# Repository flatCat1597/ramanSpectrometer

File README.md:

ramanPi
the DIY 3D Printable Raman Spectrometer

This repository will no longer contain ANY updates to the project.  The new repository at gitLab will have the latest files.  The github repo will NO LONGER be updated.  Please check the repository at https://gitlab.com/ramanPi before using any of the files here to build a ramanPi.

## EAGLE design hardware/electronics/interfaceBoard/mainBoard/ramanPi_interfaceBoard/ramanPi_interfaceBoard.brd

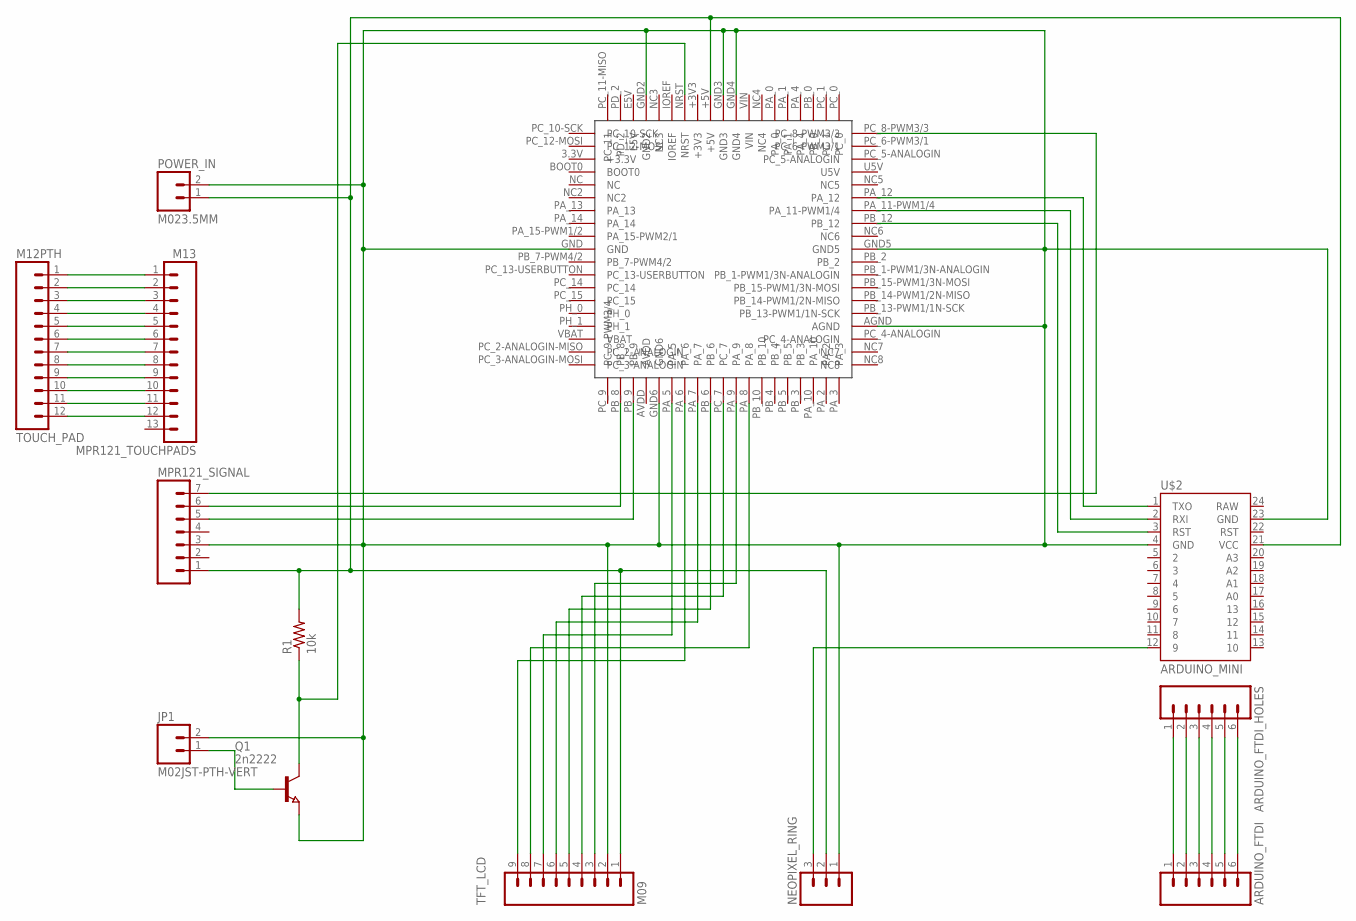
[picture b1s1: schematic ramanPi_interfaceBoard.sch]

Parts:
ARDUINO_FTDI: M06SIP; 1X06
ARDUINO_FTDI_HOLES: M06SIP; 1X06
JP1: M02JST-PTH-VERT; JST-2-PTH-VERT
MPR121_SIGNAL: M07; 1X07
MPR121_TOUCHPADS: M13; 1X13
NEOPIXEL_RING: M03JST-PTH-VERT; JST-3-PTH-VERT
POWER_IN: M023.5MM; SCREWTERMINAL-3.5MM-2
Q1: 2n2222; SOT23
R1: 10k; M1206
TFT_LCD: M09; 1X09
TOUCH_PAD: M12PTH; 1X12
U$1: STNUCLEOF401RE; F401-RE
U$2: ARDUINO_MINI

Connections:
+3.3V: U$1.3.3V (+3.3V)
+3V3: U$1.+3V3
+5V: MPR121_SIGNAL.1, NEOPIXEL_RING.2, POWER_IN.1, R1.2, TFT_LCD.1, U$1.+5V, U$2.21 (VCC)
AVDD: U$1.AVDD
E5V: U$1.E5V
GND: JP1.2, MPR121_SIGNAL.3, NEOPIXEL_RING.1, POWER_IN.2, Q1.2 (E), TFT_LCD.2, U$1.AGND, U$1.GND, U$1.GND2, U$1.GND3, U$1.GND4, U$1.GND5, U$1.GND6, U$2.4 (GND), U$2.23 (GND)
unnamed: MPR121_TOUCHPADS.1, TOUCH_PAD.1
unnamed: MPR121_TOUCHPADS.2, TOUCH_PAD.2
unnamed: MPR121_TOUCHPADS.3, TOUCH_PAD.3
unnamed: MPR121_TOUCHPADS.4, TOUCH_PAD.4
unnamed: MPR121_TOUCHPADS.5, TOUCH_PAD.5
unnamed: MPR121_TOUCHPADS.6, TOUCH_PAD.6
unnamed: MPR121_TOUCHPADS.7, TOUCH_PAD.7
unnamed: MPR121_TOUCHPADS.8, TOUCH_PAD.8
unnamed: MPR121_TOUCHPADS.9, TOUCH_PAD.9
unnamed: MPR121_TOUCHPADS.10, TOUCH_PAD.10
unnamed: MPR121_TOUCHPADS.11, TOUCH_PAD.11
unnamed: MPR121_TOUCHPADS.12, TOUCH_PAD.12
unnamed: NEOPIXEL_RING.3, U$2.12 (9)
unnamed: MPR121_SIGNAL.7, U$1.PC_8-PWM3/3
unnamed: MPR121_SIGNAL.5, U$1.PB_9
unnamed: MPR121_SIGNAL.6, U$1.PB_8
unnamed: ARDUINO_FTDI.1, ARDUINO_FTDI_HOLES.1
unnamed: ARDUINO_FTDI.2, ARDUINO_FTDI_HOLES.2
unnamed: ARDUINO_FTDI.3, ARDUINO_FTDI_HOLES.3
unnamed: ARDUINO_FTDI.4, ARDUINO_FTDI_HOLES.4
unnamed: ARDUINO_FTDI.5, ARDUINO_FTDI_HOLES.5
unnamed: ARDUINO_FTDI.6, ARDUINO_FTDI_HOLES.6
unnamed: TFT_LCD.3, U$1.PA_9
unnamed: U$1.PA_12, U$2.1 (TXO)
unnamed: U$1.PA_11-PWM1/4, U$2.2 (RXI)
unnamed: U$1.PB_12, U$2.3 (RST)
unnamed: TFT_LCD.4, U$1.PC_7
unnamed: TFT_LCD.5, U$1.PB_6
unnamed: TFT_LCD.6, U$1.PA_7
unnamed: TFT_LCD.7, U$1.PA_5
unnamed: TFT_LCD.8, U$1.PA_8
unnamed: TFT_LCD.9, U$1.PA_6
unnamed: Q1.3 (C), R1.1, U$1.NRST
unnamed: JP1.1, Q1.1 (B)
U5V: U$1.U5V
VBAT: U$1.VBAT
VIN: U$1.VIN

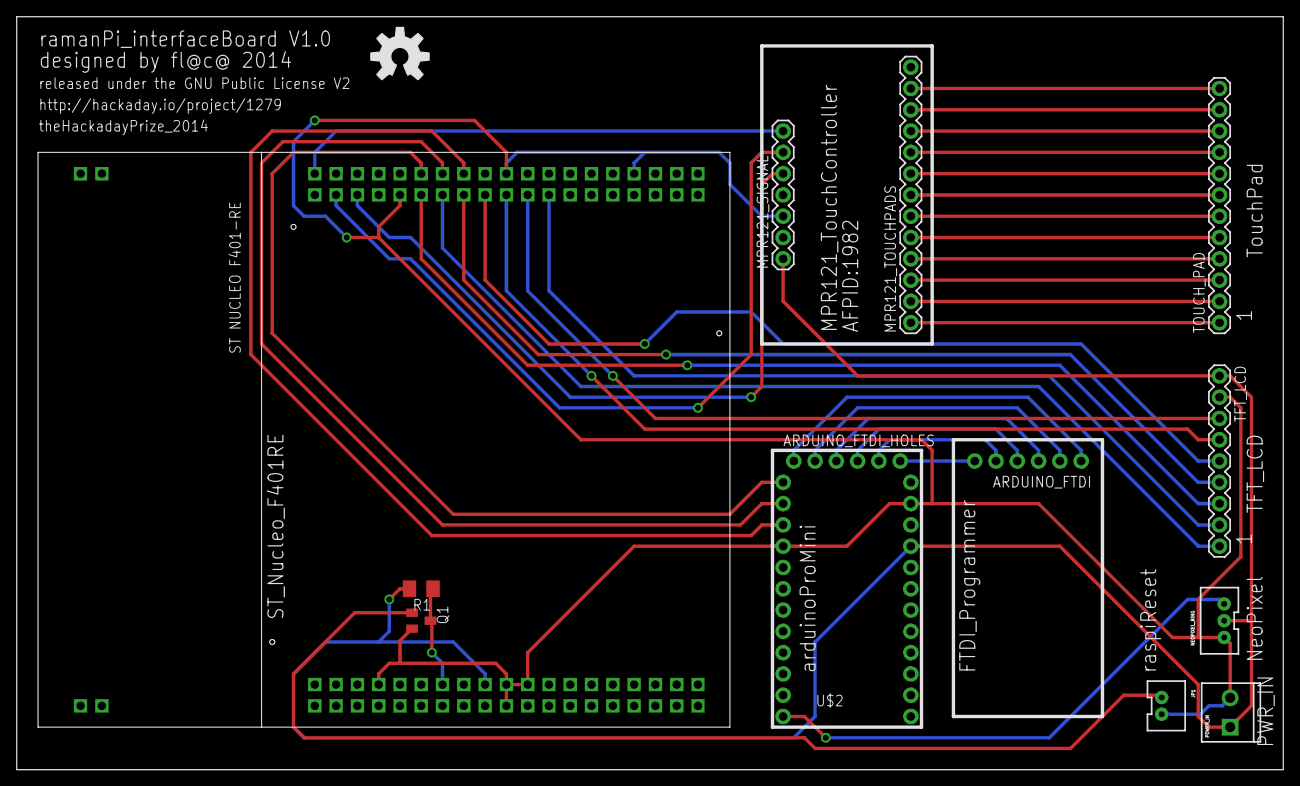
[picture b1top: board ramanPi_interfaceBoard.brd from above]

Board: 2 copper layers, 151.1 x 89.8 mm, 14 parts (0 on the bottom side), 36 nets.

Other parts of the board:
U$3: OSHW-LOGO-L

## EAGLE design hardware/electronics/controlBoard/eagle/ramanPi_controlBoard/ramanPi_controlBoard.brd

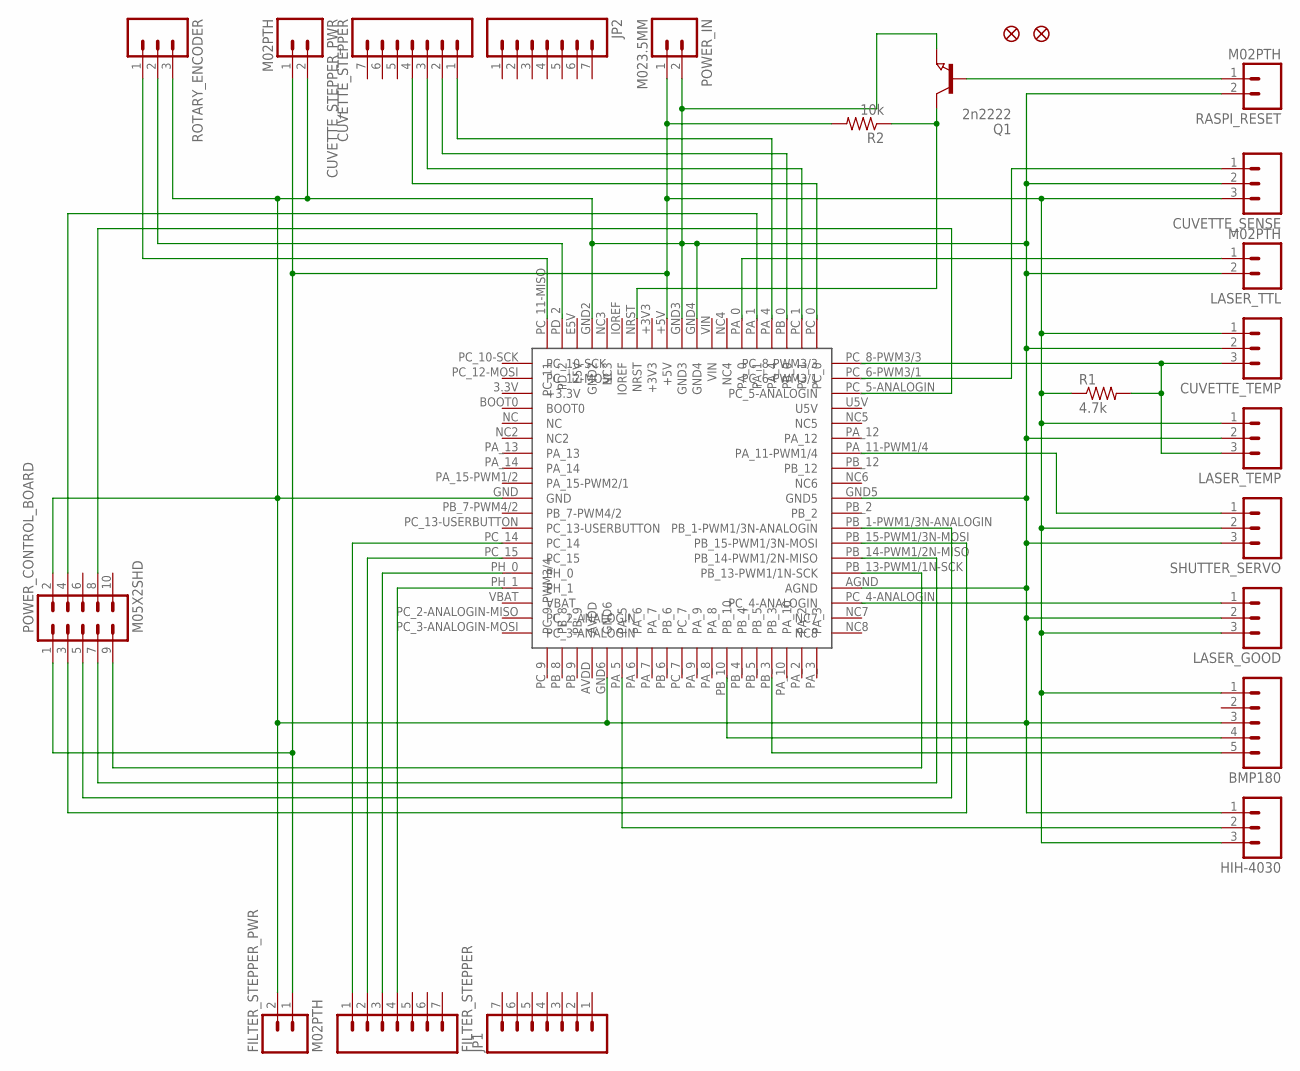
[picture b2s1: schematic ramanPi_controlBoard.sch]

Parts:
BMP180: M05PTH; 1X05
CUVETTE_SENSE: M03PTH; 1X03
CUVETTE_STEPPER: M07; 1X07
CUVETTE_STEPPER_PWR: M02PTH; 1X02
CUVETTE_TEMP: M03PTH; 1X03
FID1, FID2: FIDUCIAL1X2; FIDUCIAL-1X2
FILTER_STEPPER: M07; 1X07
FILTER_STEPPER_PWR: M02PTH; 1X02
HIH-4030: M03PTH; 1X03
JP1, JP2: M07; 1X07
LASER_GOOD: M03PTH; 1X03
LASER_TEMP: M03PTH; 1X03
LASER_TTL: M02PTH; 1X02
POWER_CONTROL_BOARD: M05X2SHD; 2X5-SHROUDED
POWER_IN: M023.5MM; SCREWTERMINAL-3.5MM-2
Q1: 2n2222; SOT23
R1: 4.7k; M1206
R2: 10k; M1206
RASPI_RESET: M02PTH; 1X02
ROTARY_ENCODER: M03PTH; 1X03
SHUTTER_SERVO: M03PTH; 1X03
U$1: STNUCLEOF401RE; F401-RE

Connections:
+3.3V: U$1.3.3V (+3.3V)
+3V3: U$1.+3V3
+5V: BMP180.1, CUVETTE_SENSE.3, CUVETTE_STEPPER_PWR.1, CUVETTE_TEMP.1, FILTER_STEPPER_PWR.1, HIH-4030.3, LASER_GOOD.3, LASER_TEMP.1, POWER_CONTROL_BOARD.1, POWER_IN.1, R1.1, R2.2, SHUTTER_SERVO.2, U$1.+5V
AVDD: U$1.AVDD
E5V: U$1.E5V
GROUND: BMP180.3, CUVETTE_SENSE.2, CUVETTE_STEPPER_PWR.2, CUVETTE_TEMP.2, FILTER_STEPPER_PWR.2, HIH-4030.1, LASER_GOOD.2, LASER_TEMP.2, LASER_TTL.2, POWER_CONTROL_BOARD.2, POWER_IN.2, Q1.2 (E), RASPI_RESET.2, ROTARY_ENCODER.3, SHUTTER_SERVO.3, U$1.AGND, U$1.GND, U$1.GND2, U$1.GND3, U$1.GND4, U$1.GND5, U$1.GND6
unnamed: BMP180.5, U$1.PB_3
unnamed: BMP180.4, U$1.PB_10
unnamed: CUVETTE_SENSE.1, U$1.PC_6-PWM3/1
unnamed: HIH-4030.2, U$1.PA_5
unnamed: CUVETTE_TEMP.3, LASER_TEMP.3, R1.2, U$1.PC_8-PWM3/3
unnamed: POWER_CONTROL_BOARD.4, U$1.PA_1
unnamed: LASER_TTL.1, U$1.PA_0
unnamed: POWER_CONTROL_BOARD.3, U$1.PB_15-PWM1/3N-MOSI
unnamed: POWER_CONTROL_BOARD.5, U$1.PB_1-PWM1/3N-ANALOG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
unnamed: POWER_CONTROL_BOARD.7, U$1.PB_14-PWM1/2N-MISO
unnamed: POWER_CONTROL_BOARD.9, U$1.PB_13-PWM1/1N-SCK
unnamed: POWER_CONTROL_BOARD.8, U$1.PC_5-ANALOGIN
unnamed: SHUTTER_SERVO.1, U$1.PA_11-PWM1/4
unnamed: LASER_GOOD.1, U$1.PC_4-ANALOGIN
unnamed: FILTER_STEPPER.1, U$1.PC_14
unnamed: FILTER_STEPPER.2, U$1.PC_15
unnamed: FILTER_STEPPER.3, U$1.PH_0
unnamed: FILTER_STEPPER.4, U$1.PH_1
unnamed: CUVETTE_STEPPER.1, U$1.PA_4
unnamed: CUVETTE_STEPPER.2, U$1.PB_0
unnamed: CUVETTE_STEPPER.3, U$1.PC_1
unnamed: CUVETTE_STEPPER.4, U$1.PC_0
unnamed: ROTARY_ENCODER.1, U$1.PC_11-MISO (PC_11)
unnamed: ROTARY_ENCODER.2, U$1.PD_2
unnamed: Q1.3 (C), R2.1, U$1.NRST
unnamed: Q1.1 (B), RASPI_RESET.1
U5V: U$1.U5V
VBAT: U$1.VBAT
VIN: U$1.VIN

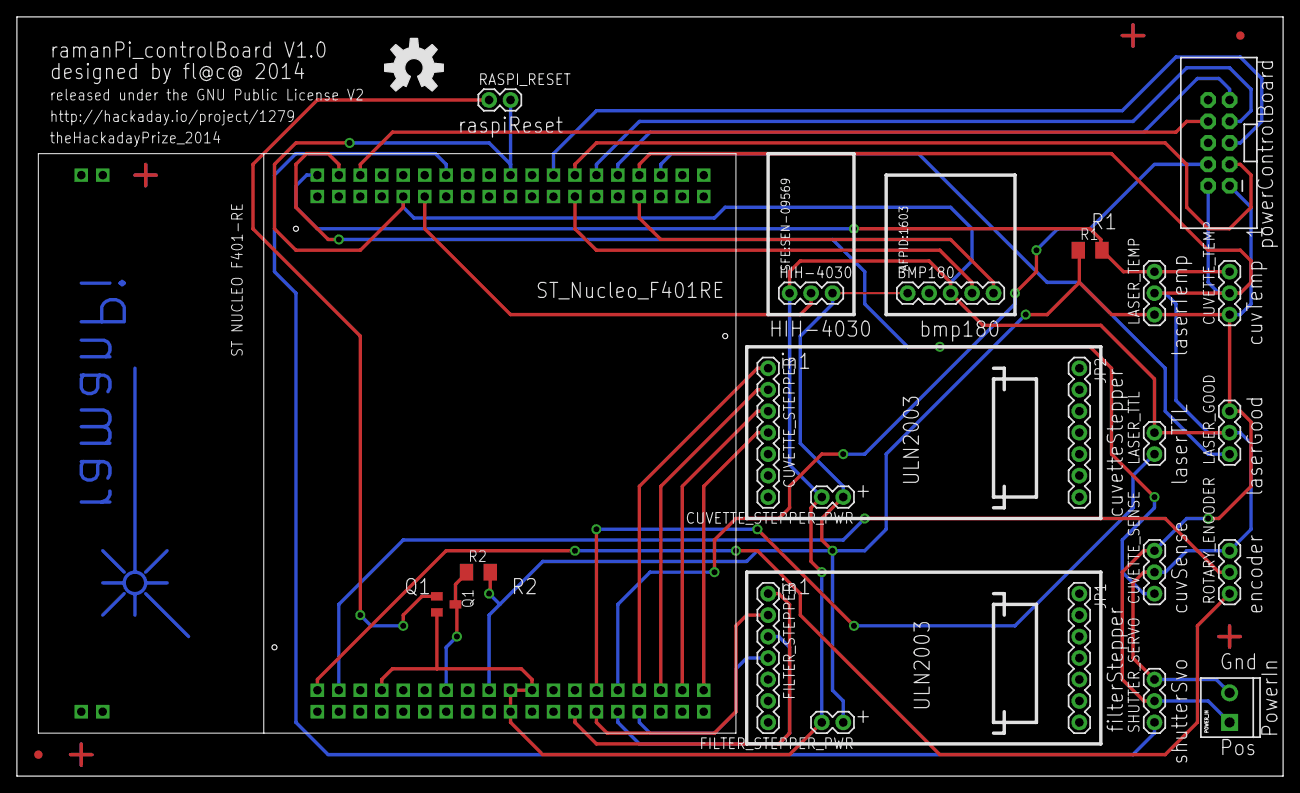
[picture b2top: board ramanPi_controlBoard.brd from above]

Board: 2 copper layers, 149.8 x 89.8 mm, 25 parts (0 on the bottom side), 28 nets.

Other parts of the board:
U$2: OSHW-LOGO-L

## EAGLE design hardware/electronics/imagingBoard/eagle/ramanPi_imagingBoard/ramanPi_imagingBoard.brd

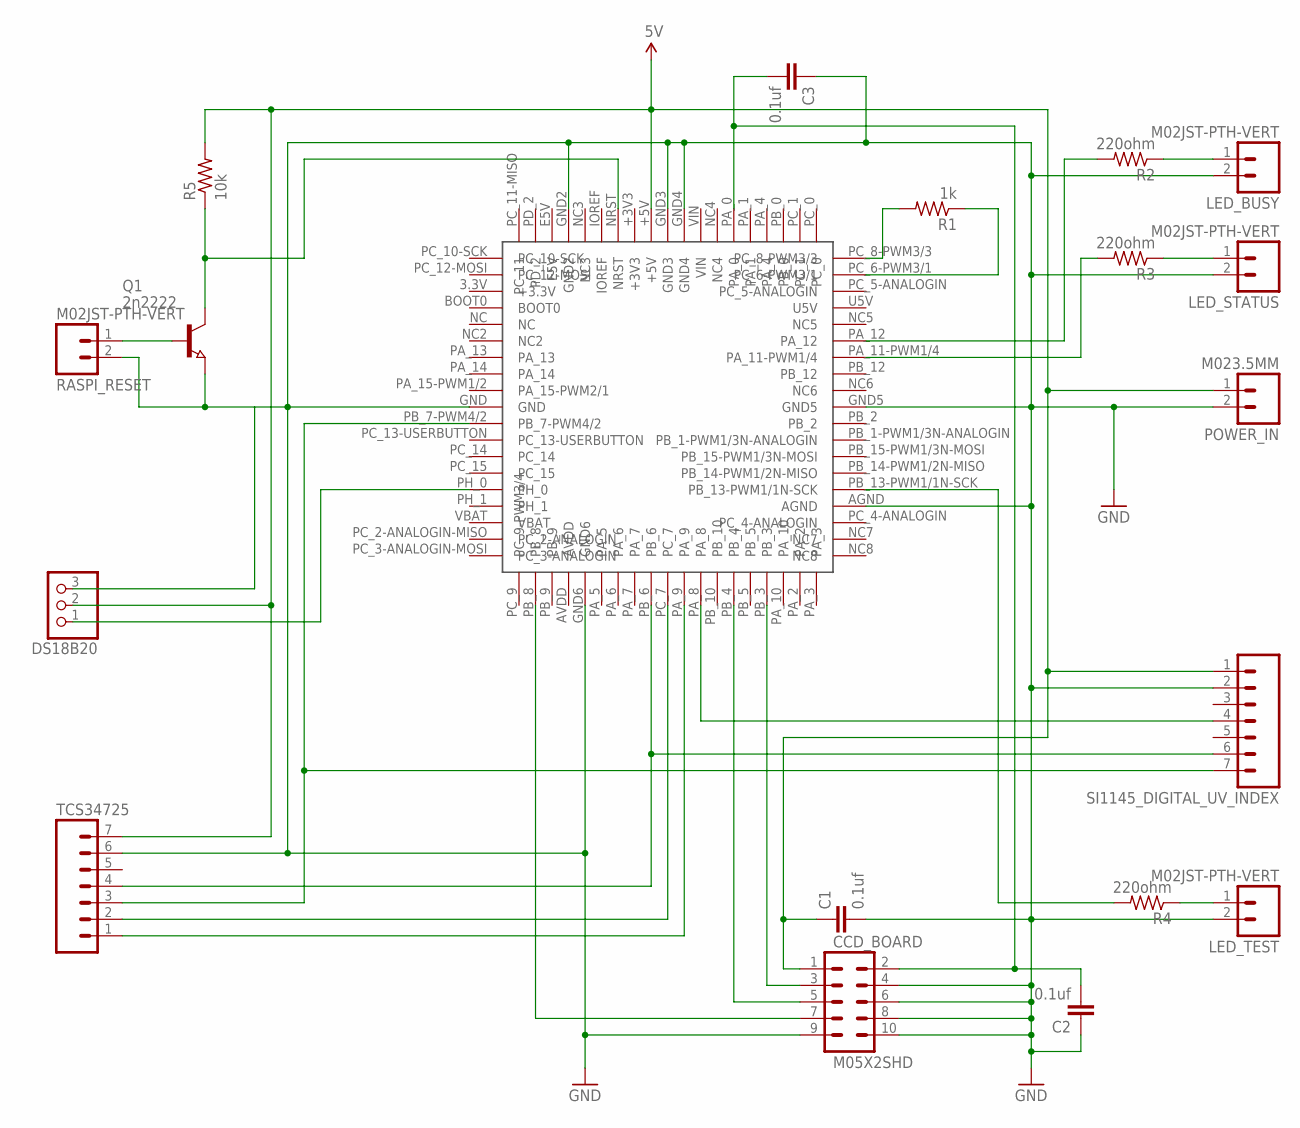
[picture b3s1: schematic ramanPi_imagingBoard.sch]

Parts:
C1, C2, C3: 0.1uf; 1210
CCD_BOARD: M05X2SHD; 2X5-SHROUDED
DS18B20: PINHD-1X3; 1X03
LED_BUSY: M02JST-PTH-VERT; JST-2-PTH-VERT
LED_STATUS: M02JST-PTH-VERT; JST-2-PTH-VERT
LED_TEST: M02JST-PTH-VERT; JST-2-PTH-VERT
POWER_IN: M023.5MM; SCREWTERMINAL-3.5MM-2
Q1: 2n2222; SOT23
R1: 1k; M1206
R2, R3, R4: 220ohm; M1206
R5: 10k; M1206
RASPI_RESET: M02JST-PTH-VERT; JST-2-PTH-VERT
SI1145_DIGITAL_UV_INDEX: M07LOCK; 1X07_LOCK
TCS34725: M07; 1X07
U$1: STNUCLEOF401RE; F401-RE

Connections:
5V: C1.1, CCD_BOARD.1, DS18B20.2, POWER_IN.1, R5.2, SI1145_DIGITAL_UV_INDEX.1, TCS34725.7, U$1.+5V
+3.3V: U$1.3.3V (+3.3V)
+3V3: U$1.+3V3
AVDD: U$1.AVDD
E5V: U$1.E5V
GND: C1.2, C2.1, C3.1, CCD_BOARD.4, CCD_BOARD.6, CCD_BOARD.8, CCD_BOARD.9, CCD_BOARD.10, DS18B20.3, LED_BUSY.2, LED_STATUS.2, LED_TEST.2, POWER_IN.2, Q1.2 (E), RASPI_RESET.2, SI1145_DIGITAL_UV_INDEX.2, TCS34725.6, U$1.AGND, U$1.GND, U$1.GND2, U$1.GND3, U$1.GND4, U$1.GND5, U$1.GND6
unnamed: CCD_BOARD.7, U$1.PB_8
unnamed: CCD_BOARD.5, U$1.PB_4
unnamed: Q1.1 (B), RASPI_RESET.1
unnamed: R1.2, U$1.PC_8-PWM3/3
unnamed: R1.1, U$1.PC_6-PWM3/1
unnamed: DS18B20.1, U$1.PH_0
unnamed: SI1145_DIGITAL_UV_INDEX.7, TCS34725.3, U$1.PB_7-PWM4/2
unnamed: SI1145_DIGITAL_UV_INDEX.6, TCS34725.4, U$1.PB_6
unnamed: C2.2, C3.2, CCD_BOARD.2, U$1.PA_0
unnamed: SI1145_DIGITAL_UV_INDEX.4, U$1.PA_8
unnamed: TCS34725.2, U$1.PC_7
unnamed: TCS34725.1, U$1.PA_9
unnamed: LED_BUSY.1, R2.1
unnamed: LED_STATUS.1, R3.1
unnamed: LED_TEST.1, R4.1
unnamed: R2.2, U$1.PA_12
unnamed: R3.2, U$1.PA_11-PWM1/4
unnamed: R4.2, U$1.PB_13-PWM1/1N-SCK
unnamed: Q1.3 (C), R5.1, U$1.NRST
unnamed: CCD_BOARD.3, U$1.PB_3
U5V: U$1.U5V
VBAT: U$1.VBAT
VIN: U$1.VIN

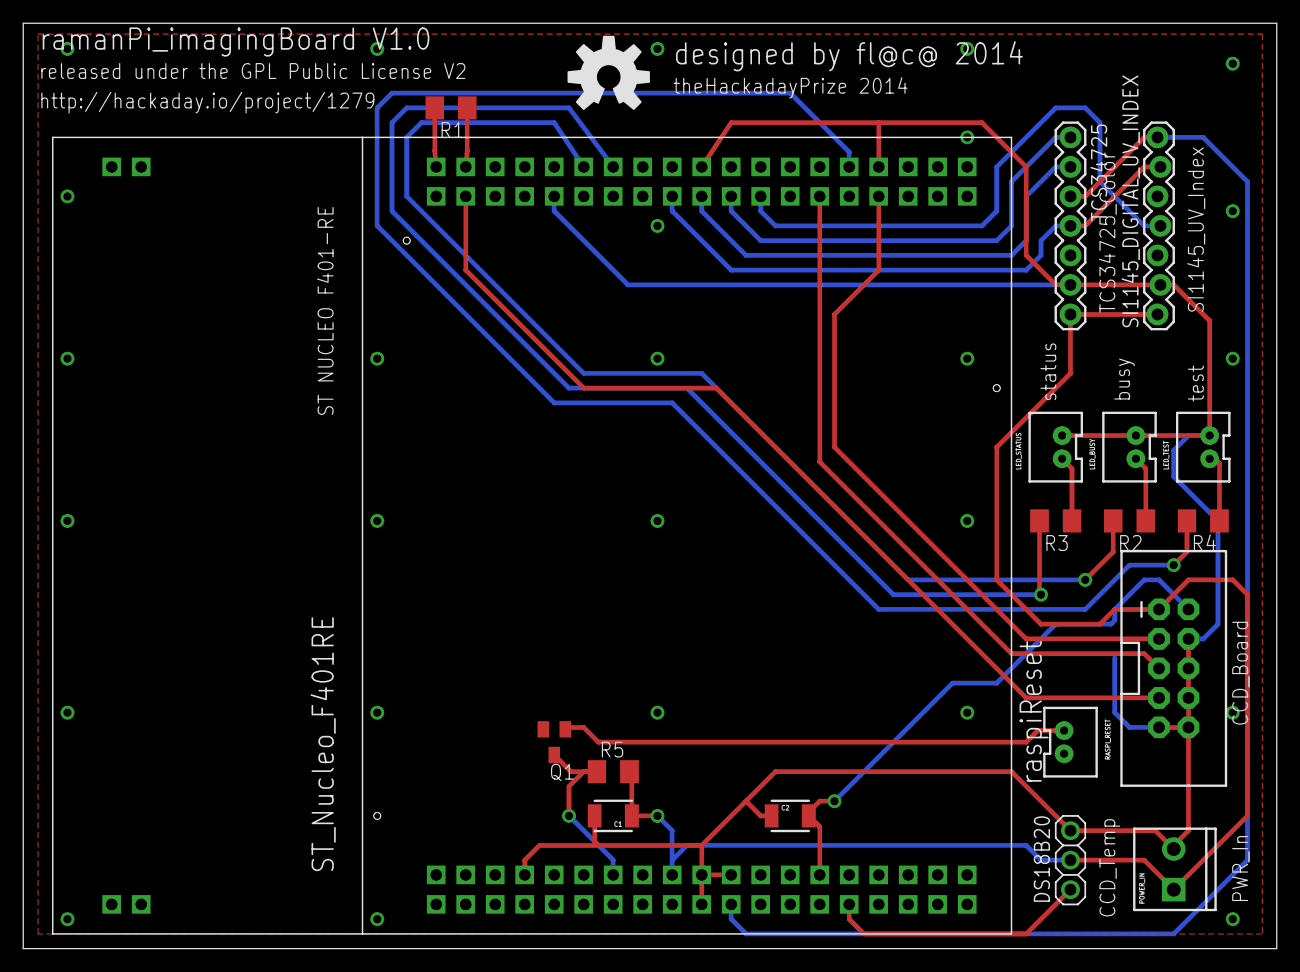
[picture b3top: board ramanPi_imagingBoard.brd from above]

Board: 2 copper layers, 107.9 x 79.7 mm, 20 parts (1 on the bottom side), 22 nets.

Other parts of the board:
U$2: OSHW-LOGO-L

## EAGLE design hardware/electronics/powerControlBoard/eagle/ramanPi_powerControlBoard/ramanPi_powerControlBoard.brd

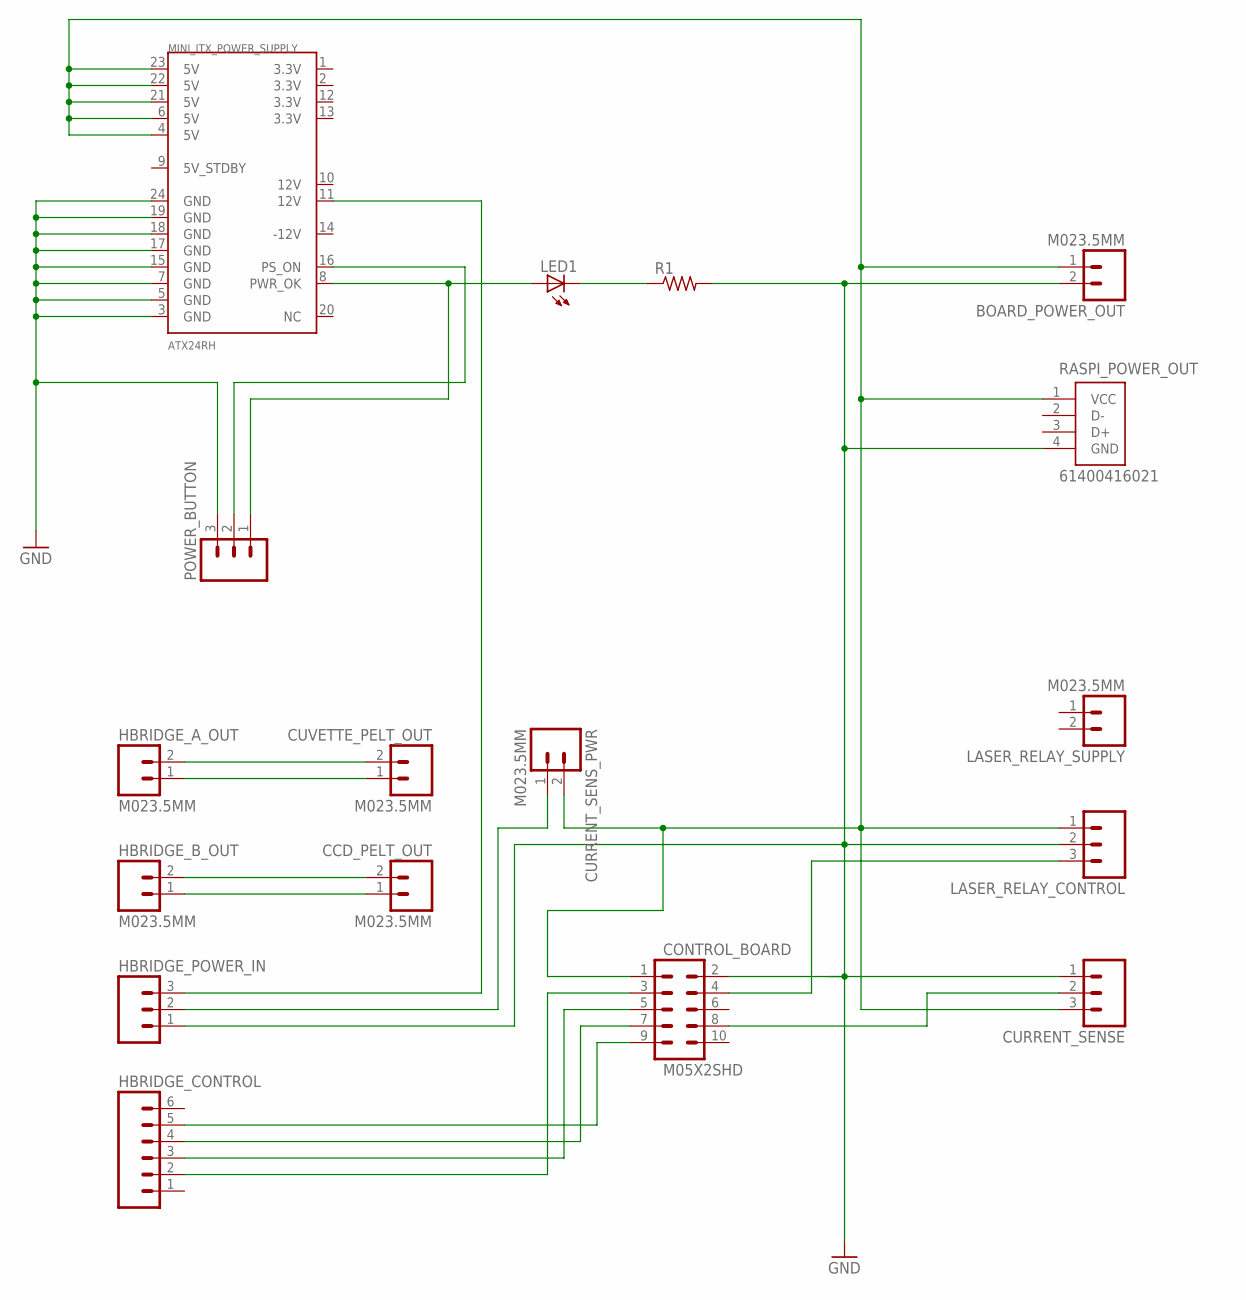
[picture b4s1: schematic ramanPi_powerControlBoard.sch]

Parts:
BOARD_POWER_OUT: M023.5MM; SCREWTERMINAL-3.5MM-2
CCD_PELT_OUT: M023.5MM; SCREWTERMINAL-3.5MM-2
CONTROL_BOARD: M05X2SHD; 2X5-SHROUDED
CURRENT_SENSE: M03PTH; 1X03
CURRENT_SENS_PWR: M023.5MM; SCREWTERMINAL-3.5MM-2
CUVETTE_PELT_OUT: M023.5MM; SCREWTERMINAL-3.5MM-2
HBRIDGE_A_OUT: M023.5MM; SCREWTERMINAL-3.5MM-2
HBRIDGE_B_OUT: M023.5MM; SCREWTERMINAL-3.5MM-2
HBRIDGE_CONTROL: M06SIP; 1X06
HBRIDGE_POWER_IN: M03SCREW; SCREWTERMINAL-3.5MM-3
LASER_RELAY_CONTROL: M03PTH; 1X03
LASER_RELAY_SUPPLY: M023.5MM; SCREWTERMINAL-3.5MM-2
LED1: LED5MM
MINI_ITX_POWER_SUPPLY: ATX24RH; ATX24_RIGHT_ANGLE
POWER_BUTTON: M03JST-PTH-VERT; JST-3-PTH-VERT
R1: R-US_M1206; M1206
RASPI_POWER_OUT: 61400416021

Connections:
GND: BOARD_POWER_OUT.2, CONTROL_BOARD.2, CURRENT_SENSE.1, HBRIDGE_POWER_IN.1, LASER_RELAY_CONTROL.2, MINI_ITX_POWER_SUPPLY.3 (GND), MINI_ITX_POWER_SUPPLY.5 (GND), MINI_ITX_POWER_SUPPLY.7 (GND), MINI_ITX_POWER_SUPPLY.15 (GND), MINI_ITX_POWER_SUPPLY.17 (GND), MINI_ITX_POWER_SUPPLY.18 (GND), MINI_ITX_POWER_SUPPLY.19 (GND), MINI_ITX_POWER_SUPPLY.24 (GND), POWER_BUTTON.3, R1.2, RASPI_POWER_OUT.4 (GND)
unnamed: CONTROL_BOARD.4, LASER_RELAY_CONTROL.3
unnamed: LED1.A, MINI_ITX_POWER_SUPPLY.8 (PWR_OK), POWER_BUTTON.1
unnamed: CONTROL_BOARD.8, CURRENT_SENSE.2
unnamed: MINI_ITX_POWER_SUPPLY.16 (PS_ON), POWER_BUTTON.2
unnamed: LED1.K (C), R1.1
unnamed: CONTROL_BOARD.9, HBRIDGE_CONTROL.5
unnamed: HBRIDGE_POWER_IN.3, MINI_ITX_POWER_SUPPLY.11 (12V)
unnamed: CUVETTE_PELT_OUT.1, HBRIDGE_A_OUT.1
unnamed: CUVETTE_PELT_OUT.2, HBRIDGE_A_OUT.2
unnamed: CCD_PELT_OUT.2, HBRIDGE_B_OUT.2
unnamed: CCD_PELT_OUT.1, HBRIDGE_B_OUT.1
unnamed: CONTROL_BOARD.7, HBRIDGE_CONTROL.4
unnamed: CONTROL_BOARD.5, HBRIDGE_CONTROL.3
unnamed: CONTROL_BOARD.3, HBRIDGE_CONTROL.2
unnamed: CURRENT_SENS_PWR.1, HBRIDGE_POWER_IN.2
unnamed: BOARD_POWER_OUT.1, CONTROL_BOARD.1, CURRENT_SENSE.3, CURRENT_SENS_PWR.2, LASER_RELAY_CONTROL.1, MINI_ITX_POWER_SUPPLY.4 (5V), MINI_ITX_POWER_SUPPLY.6 (5V), MINI_ITX_POWER_SUPPLY.21 (5V), MINI_ITX_POWER_SUPPLY.22 (5V), MINI_ITX_POWER_SUPPLY.23 (5V), RASPI_POWER_OUT.1 (VCC)

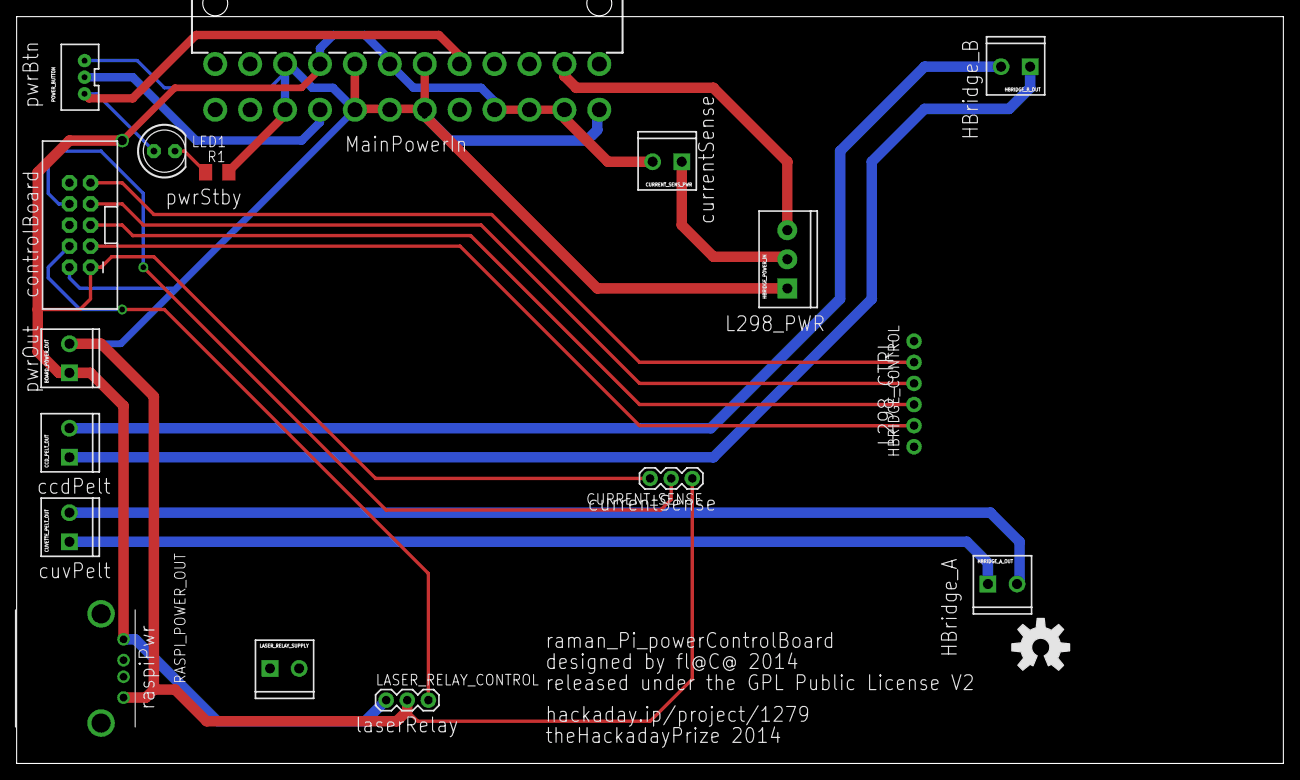
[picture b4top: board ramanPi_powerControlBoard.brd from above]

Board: 2 copper layers, 152.4 x 89.8 mm, 19 parts (1 on the bottom side), 17 nets.

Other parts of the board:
U$1, U$2: OSHW-LOGO-L

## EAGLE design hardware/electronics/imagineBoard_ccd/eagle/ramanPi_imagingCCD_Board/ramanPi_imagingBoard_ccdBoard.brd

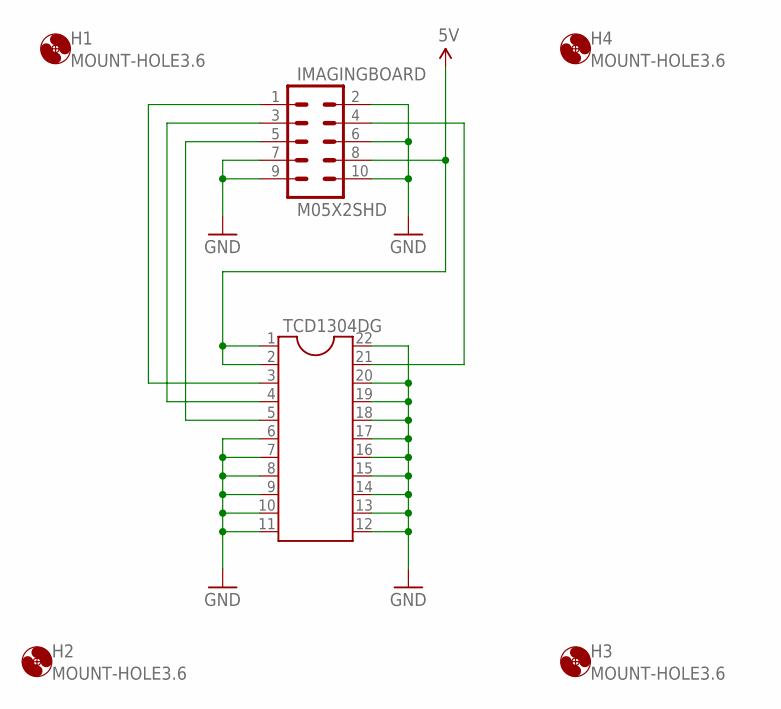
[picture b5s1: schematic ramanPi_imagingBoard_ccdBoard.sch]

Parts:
H1, H2, H3, H4: MOUNT-HOLE3.6; 3,6
IMAGINGBOARD: M05X2SHD; 2X5-SHROUDED
TCD1304DG: DIL22-4

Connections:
5V: IMAGINGBOARD.8, TCD1304DG.1, TCD1304DG.2
GND: IMAGINGBOARD.2, IMAGINGBOARD.6, IMAGINGBOARD.7, IMAGINGBOARD.9, IMAGINGBOARD.10, TCD1304DG.6, TCD1304DG.7, TCD1304DG.8, TCD1304DG.9, TCD1304DG.10, TCD1304DG.11, TCD1304DG.12, TCD1304DG.13, TCD1304DG.14, TCD1304DG.15, TCD1304DG.16, TCD1304DG.17, TCD1304DG.18, TCD1304DG.19, TCD1304DG.20, TCD1304DG.22
unnamed: IMAGINGBOARD.1, TCD1304DG.3
unnamed: IMAGINGBOARD.3, TCD1304DG.4
unnamed: IMAGINGBOARD.5, TCD1304DG.5
unnamed: IMAGINGBOARD.4, TCD1304DG.21

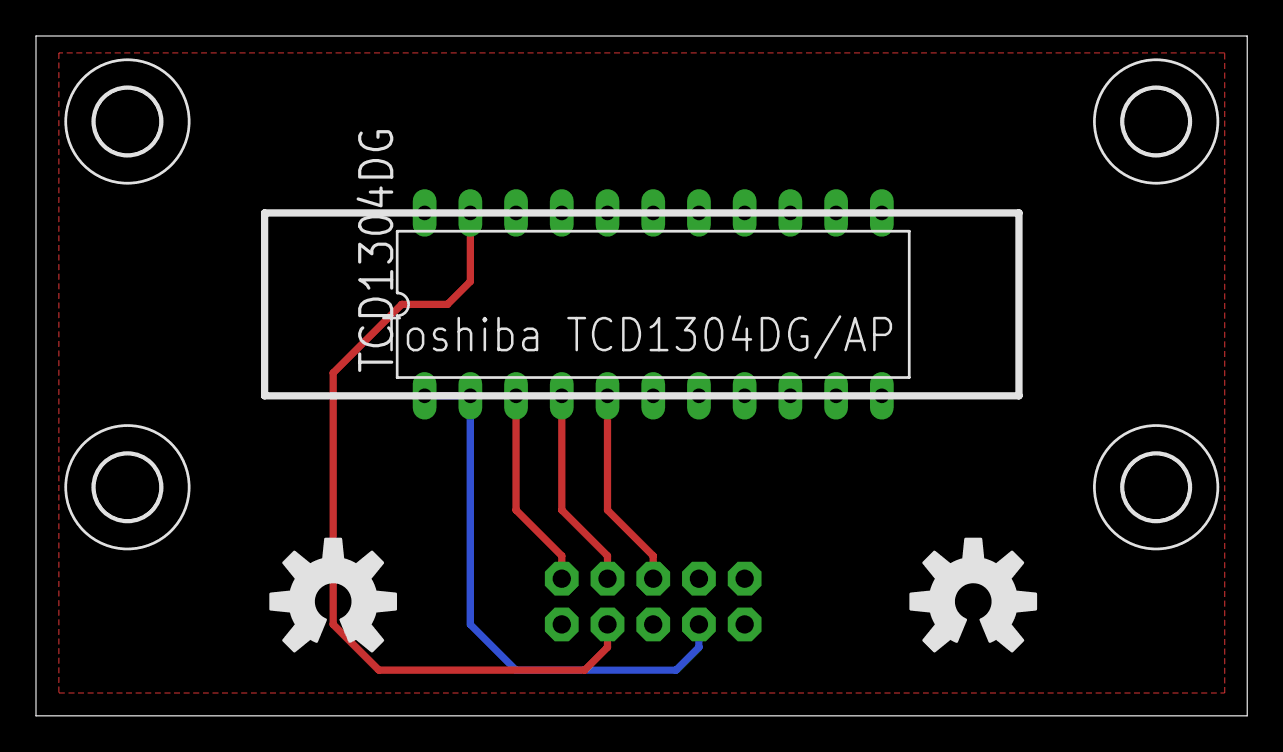
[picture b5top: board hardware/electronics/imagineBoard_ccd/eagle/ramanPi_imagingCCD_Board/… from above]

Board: 2 copper layers, 67.3 x 37.8 mm, 8 parts (1 on the bottom side), 6 nets.

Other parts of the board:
U$1, U$2: OSHW-LOGO-L

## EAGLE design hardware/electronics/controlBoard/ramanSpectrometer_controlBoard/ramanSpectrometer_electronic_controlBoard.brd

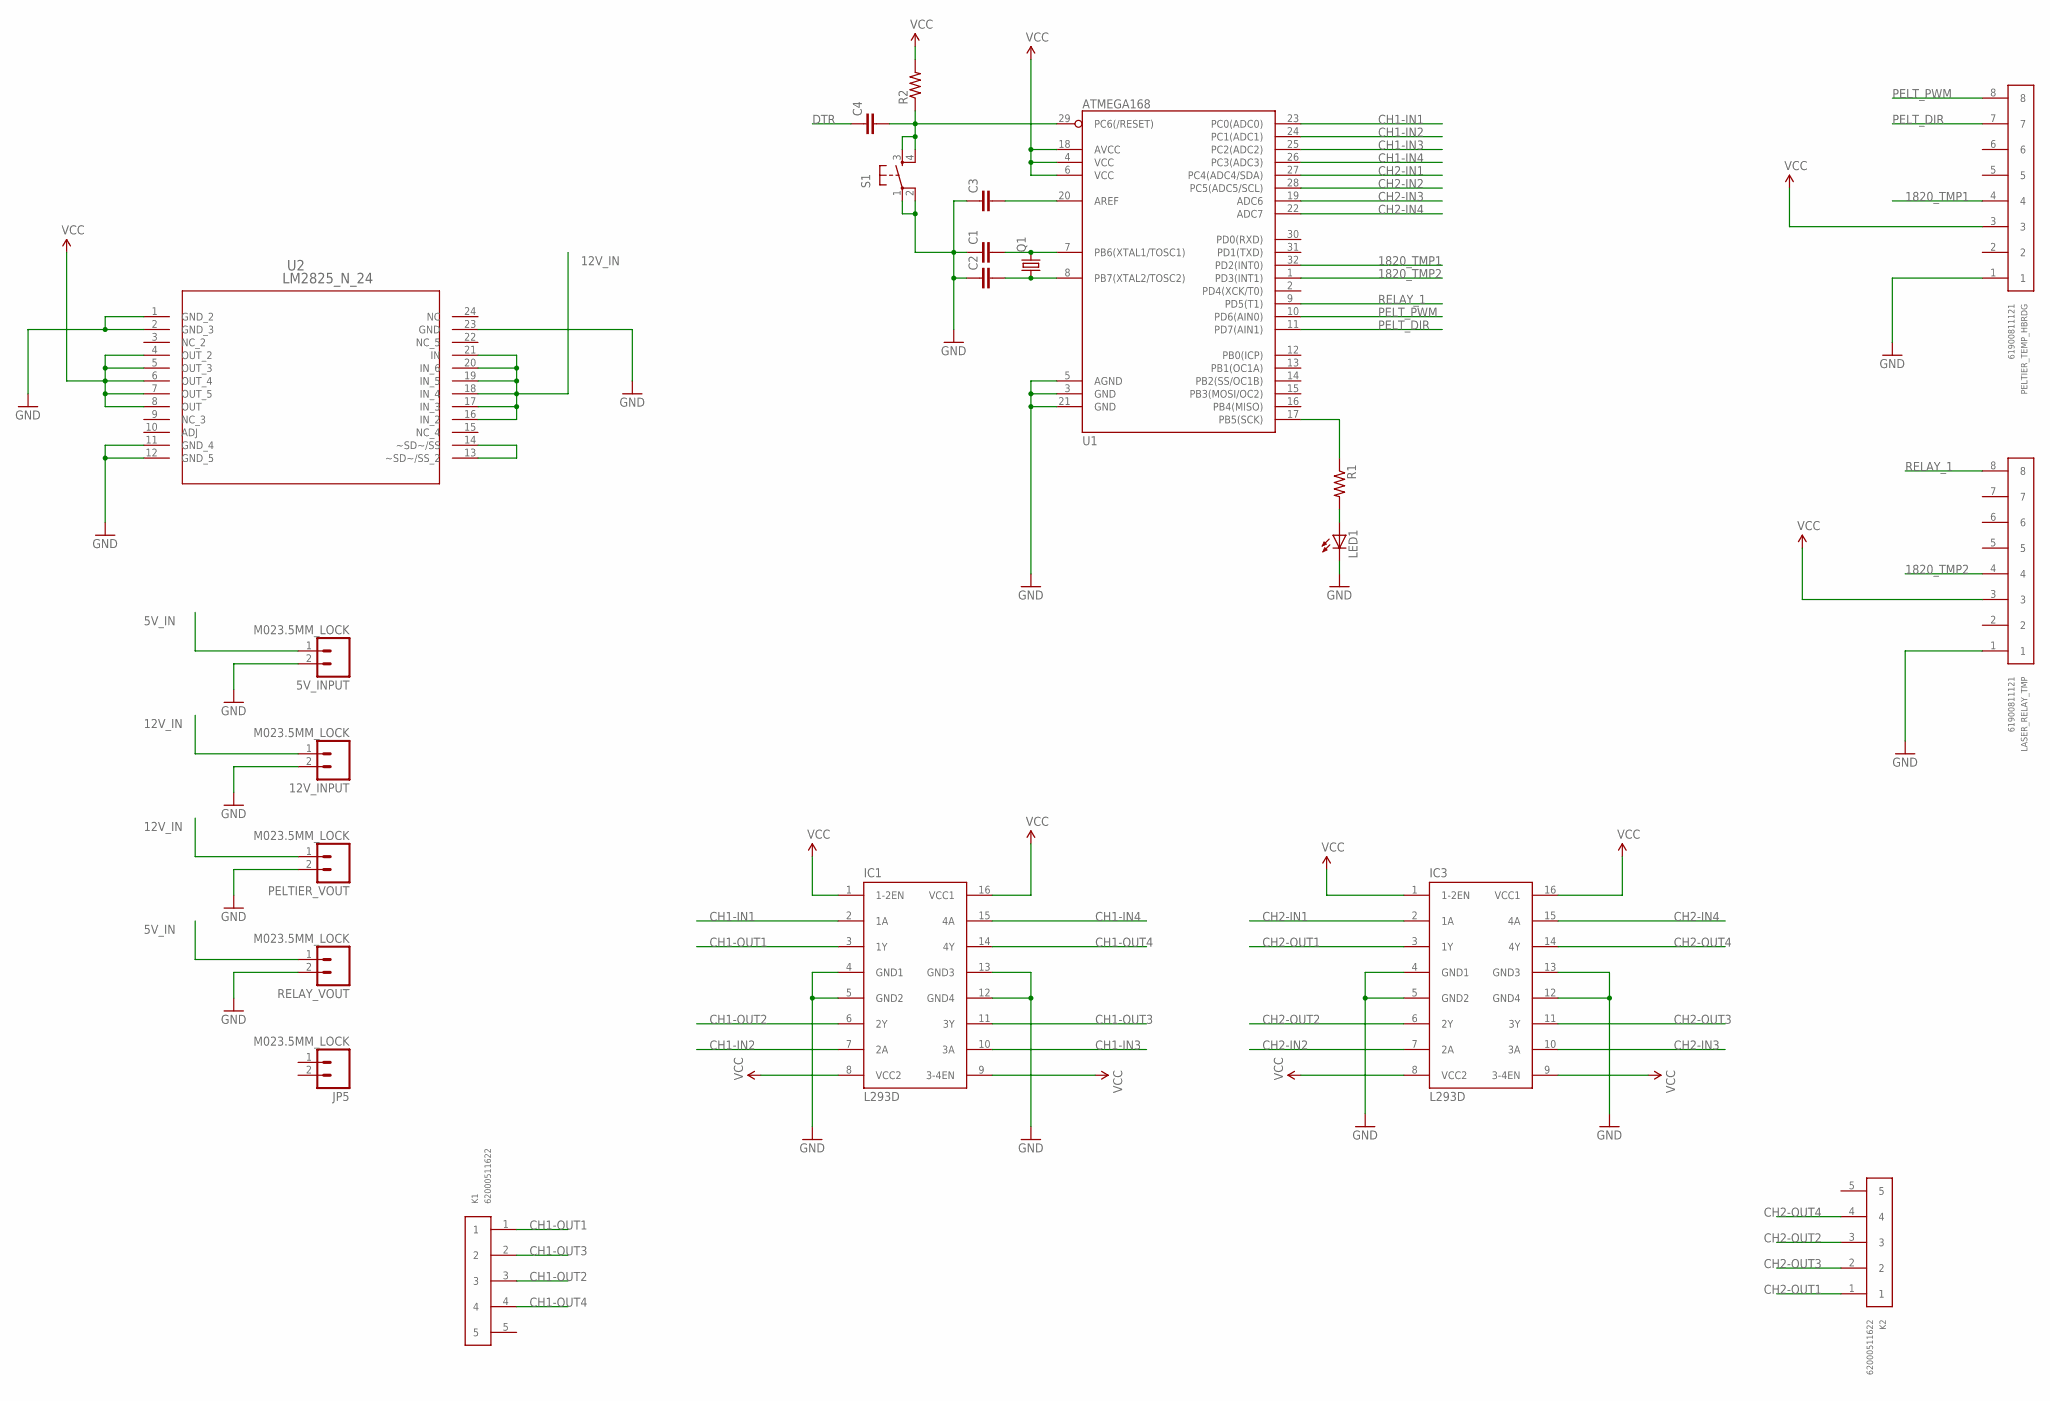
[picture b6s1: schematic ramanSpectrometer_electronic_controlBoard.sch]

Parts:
5V_INPUT, 12V_INPUT: M023.5MM_LOCK; SCREWTERMINAL-3.5MM-2_LOCK
C1, C2: CAP1206; 1206
C3, C4: CAP1210; 1210
IC1, IC3: L293D; DIL16
JP5: M023.5MM_LOCK; SCREWTERMINAL-3.5MM-2_LOCK
K1, K2: 62000511622
LASER_RELAY_TMP: 61900811121
LED1: LEDP-LCC-2; P-LCC-2
PELTIER_TEMP_HBRDG: 61900811121
PELTIER_VOUT: M023.5MM_LOCK; SCREWTERMINAL-3.5MM-2_LOCK
Q1: CRYSTALSM49; SM49
R1, R2: RESISTOR1206; 1206
RELAY_VOUT: M023.5MM_LOCK; SCREWTERMINAL-3.5MM-2_LOCK
S1: TAC_SWITCHSMD; TACTILE_SWITCH_SMD
U1: ATMEGA168; TQFP32-08
U2: LM2825_N_24; NA24F

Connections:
5V_IN: 5V_INPUT.1, RELAY_VOUT.1
12V_IN: 12V_INPUT.1, PELTIER_VOUT.1, U2.16 (IN_2), U2.17 (IN_3), U2.18 (IN_4), U2.19 (IN_5), U2.20 (IN_6), U2.21 (IN)
1820_TMP1: PELTIER_TEMP_HBRDG.4, U1.32 (PD2(INT0))
1820_TMP2: LASER_RELAY_TMP.4, U1.1 (PD3(INT1))
CH1-IN1: IC1.2 (1A), U1.23 (PC0(ADC0))
CH1-IN2: IC1.7 (2A), U1.24 (PC1(ADC1))
CH1-IN3: IC1.10 (3A), U1.25 (PC2(ADC2))
CH1-IN4: IC1.15 (4A), U1.26 (PC3(ADC3))
CH1-OUT1: IC1.3 (1Y), K1.1
CH1-OUT2: IC1.6 (2Y), K1.3
CH1-OUT3: IC1.11 (3Y), K1.2
CH1-OUT4: IC1.14 (4Y), K1.4
CH2-IN1: IC3.2 (1A), U1.27 (PC4(ADC4/SDA))
CH2-IN2: IC3.7 (2A), U1.28 (PC5(ADC5/SCL))
CH2-IN3: IC3.10 (3A), U1.19 (ADC6)
CH2-IN4: IC3.15 (4A), U1.22 (ADC7)
CH2-OUT1: IC3.3 (1Y), K2.1
CH2-OUT2: IC3.6 (2Y), K2.3
CH2-OUT3: IC3.11 (3Y), K2.2
CH2-OUT4: IC3.14 (4Y), K2.4
DTR: C4.1
GND: 5V_INPUT.2, 12V_INPUT.2, C1.1, C2.1, C3.1, IC1.4 (GND1), IC1.5 (GND2), IC1.12 (GND4), IC1.13 (GND3), IC3.4 (GND1), IC3.5 (GND2), IC3.12 (GND4), IC3.13 (GND3), LASER_RELAY_TMP.1, LED1.C, PELTIER_TEMP_HBRDG.1, PELTIER_VOUT.2, RELAY_VOUT.2, S1.1, S1.2, U1.3 (GND), U1.5 (AGND), U1.21 (GND), U2.1 (GND_2), U2.2 (GND_3), U2.11 (GND_4), U2.12 (GND_5), U2.23 (GND)
unnamed: LED1.A, R1.2
unnamed: R1.1, U1.17 (PB5(SCK))
unnamed: C1.2, Q1.2, U1.7 (PB6(XTAL1/TOSC1))
unnamed: C3.2, U1.20 (AREF)
unnamed: C2.2, Q1.1, U1.8 (PB7(XTAL2/TOSC2))
unnamed: C4.2, R2.1, S1.3, S1.4, U1.29 (PC6(/RESET))
unnamed: U2.13 (~SD~/SS_2), U2.14 (~SD~/SS)
PELT_DIR: PELTIER_TEMP_HBRDG.7, U1.11 (PD7(AIN1))
PELT_PWM: PELTIER_TEMP_HBRDG.8, U1.10 (PD6(AIN0))
RELAY_1: LASER_RELAY_TMP.8, U1.9 (PD5(T1))
VCC: IC1.1 (1-2EN), IC1.8 (VCC2), IC1.9 (3-4EN), IC1.16 (VCC1), IC3.1 (1-2EN), IC3.8 (VCC2), IC3.9 (3-4EN), IC3.16 (VCC1), LASER_RELAY_TMP.3, PELTIER_TEMP_HBRDG.3, R2.2, U1.4 (VCC), U1.6 (VCC), U1.18 (AVCC), U2.4 (OUT_2), U2.5 (OUT_3), U2.6 (OUT_4), U2.7 (OUT_5), U2.8 (OUT)

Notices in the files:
hardware/electronics/controlBoard/eagle/ramanPi_controlBoard/ramanPi_controlBoard.brd:
released under the GNU Public License V2
hardware/electronics/imagineBoard_ccd/eagle/ramanPi_imagingBoard_ccd/ramanPi_imagingBoard_ccdBoard.brd:
released under the GPL Public License V2
parts and their libraries:
SparkFun-Connectors: Licensing: Creative Commons ShareAlike 4.0 International - https://creativecommons.org/licenses/by-sa/4.0
Wuerth_Elektronik_eiCan_Wire_to_Board_Co: Copyright: Würth Elektronik
